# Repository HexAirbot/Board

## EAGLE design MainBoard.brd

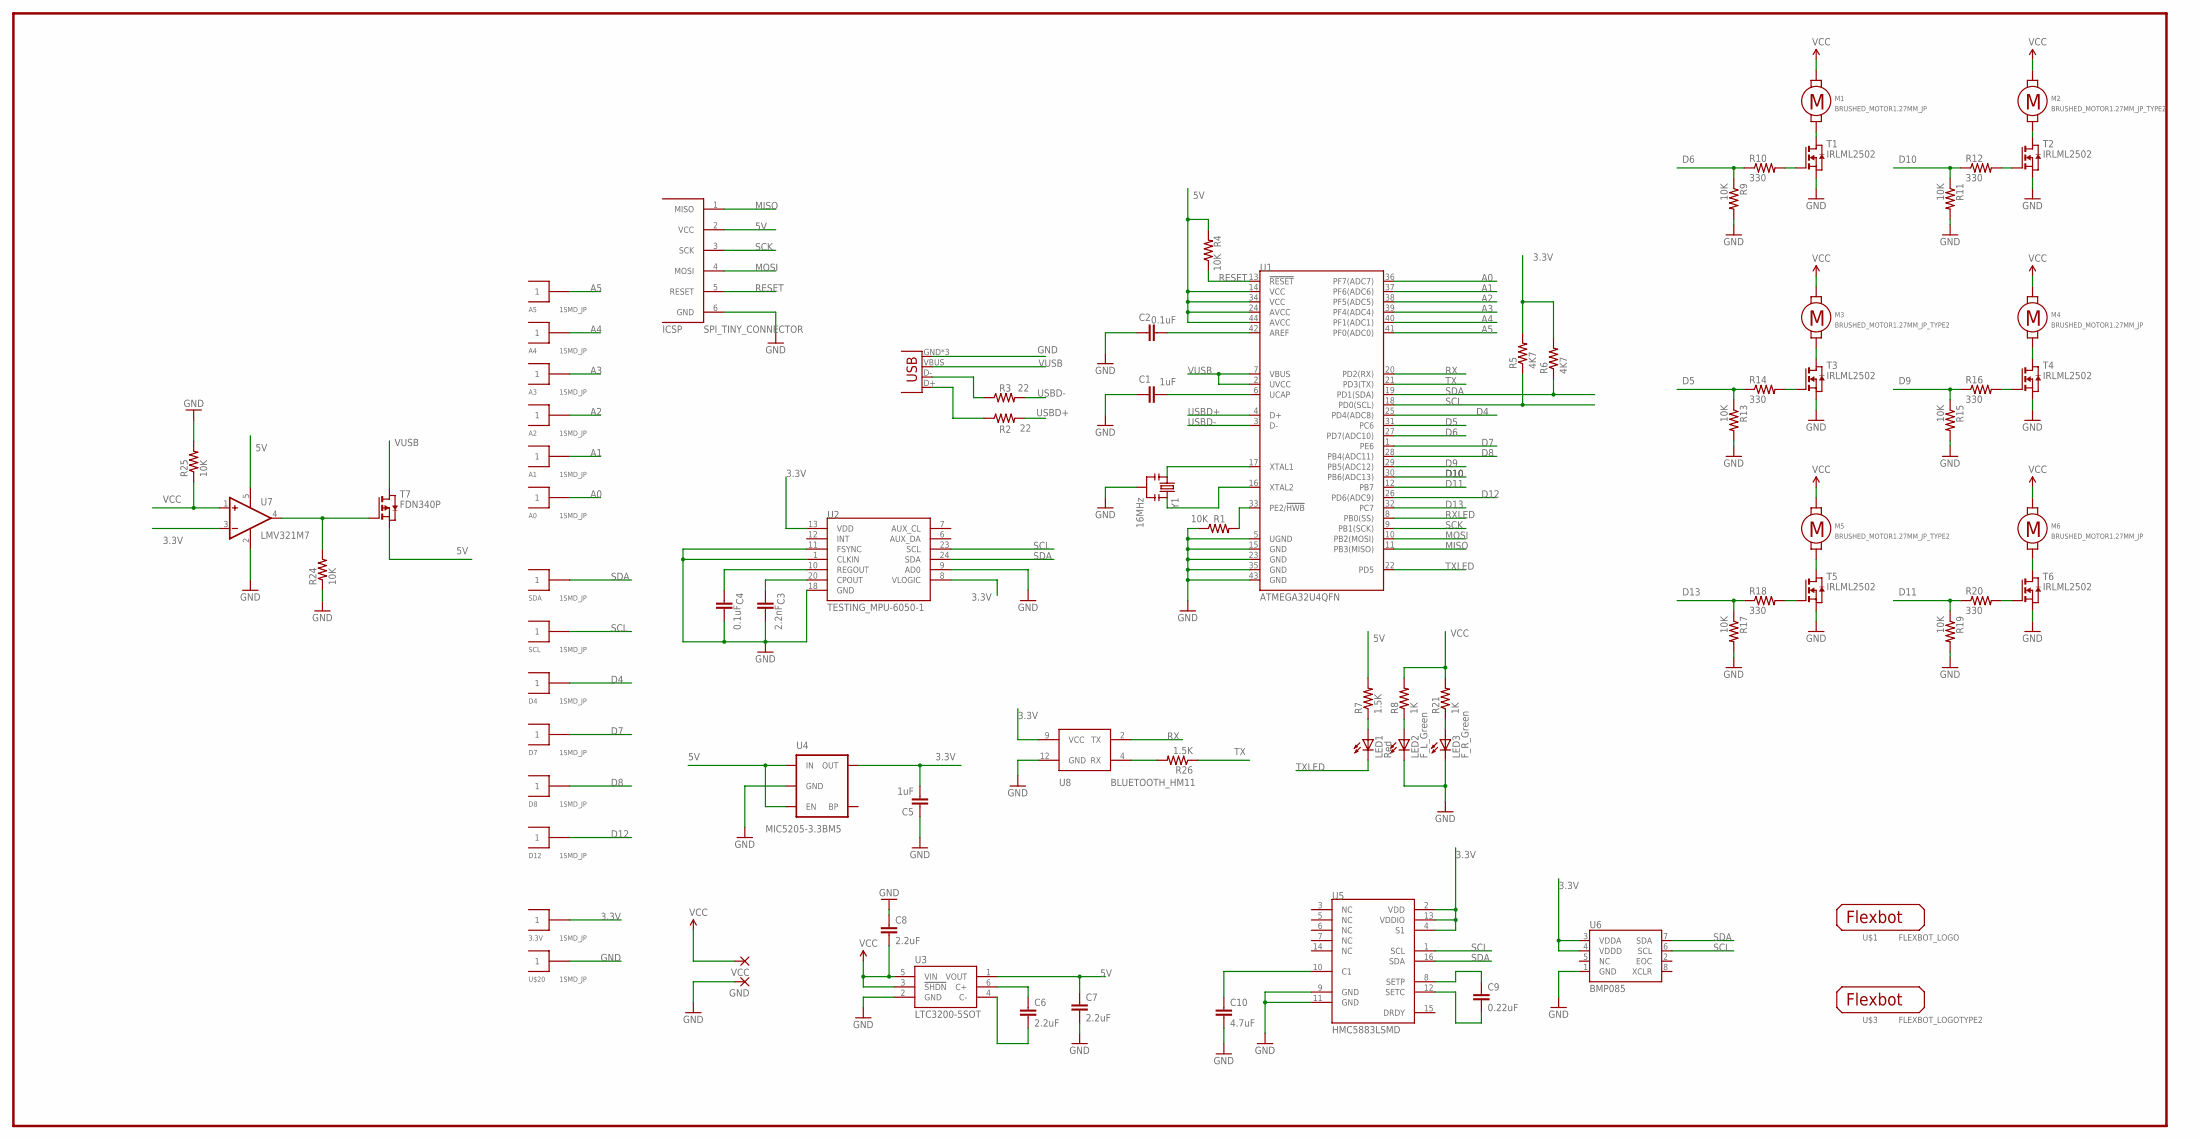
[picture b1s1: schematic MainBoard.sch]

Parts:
3.3V: 1SMD_JP; 1SMD
A0, A1, A2, A3, A4, A5: 1SMD_JP; 1SMD
C1, C5: 1uF; 0402-CAP
C2, C4: 0.1uF; 0402-CAP
C3: 2.2nF; 0402-CAP
C6, C7, C8: 2.2uF; 0603-CAP
C9: 0.22uF; 0402-CAP
C10: 4.7uF; 0603-CAP
D4, D7, D8, D12: 1SMD_JP; 1SMD
GND: 2,15/1,0
ICSP: SPI_TINY_CONNECTOR; AVR_ISP_TINY_CONNECTOR_NO_BORDER
JP1: USB-MICROB
LED1: Red; CHIPLED_0603
LED2: F_L_Green; CHIPLED_0603
LED3: F_R_Green; CHIPLED_0603
M1, M4, M6: BRUSHED_MOTOR1.27MM_JP; BRUSHED_MOTOR_1.27MM_JP
M2, M3, M5: BRUSHED_MOTOR1.27MM_JP_TYPE2; BRUSHED_MOTOR_1.27MM_JP_TYPE2
R1, R4, R9, R11, R13, R15, R17, R19, R24, R25: 10K; 0402-RES
R2, R3: 22; 0402-RES
R5, R6: 4K7; 0402-RES
R7, R26: 1.5K; 0402-RES
R8, R21: 1K; 0402-RES
R10, R12, R14, R16, R18, R20: 330; 0402-RES
SCL: 1SMD_JP; 1SMD
SDA: 1SMD_JP; 1SMD
T1, T2, T3, T4, T5, T6: IRLML2502; SOT-23
T7: FDN340P; SOT23
U1: ATMEGA32U4QFN; SPARKFUN-DIGITALIC_QFN-44
U2: TESTING_MPU-6050-1; TESTING_QFN-24-4MM2
U3: LTC3200-5SOT; SOT23-6
U4: MIC5205-3.3BM5; SOT23-5
U5: HMC5883LSMD; 16LPCC
U6: BMP085
U7: LMV321M7; SC70-5L
U8: BLUETOOTH_HM11
U$1: FLEXBOT_LOGO
U$3: FLEXBOT_LOGOTYPE2; FLEXBOT_LOGO_TYPE2
U$20: 1SMD_JP; 1SMD
VCC: 2,15/1,0
Y1: 16MHz; RESONATOR-SMD

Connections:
3.3V: 3.3V.1, C5.2, R5.2, R6.2, U2.8 (VLOGIC), U2.13 (VDD), U4.5 (OUT), U5.2 (VDD), U5.4 (S1), U5.13 (VDDIO), U6.3 (VDDA), U6.4 (VDDD), U7.3 (-IN), U8.9 (VCC)
5V: C7.1, ICSP.2 (VCC), R4.2, R7.2, T7.2 (S), U1.14 (VCC), U1.24 (AVCC), U1.34 (VCC), U1.44 (AVCC), U3.1 (VOUT), U4.1 (IN), U4.3 (EN), U7.5 (V+)
A0: A0.1, U1.36 (PF7(ADC7))
A1: A1.1, U1.37 (PF6(ADC6))
A2: A2.1, U1.38 (PF5(ADC5))
A3: A3.1, U1.39 (PF4(ADC4))
A4: A4.1, U1.40 (PF1(ADC1))
A5: A5.1, U1.41 (PF0(ADC0))
D4: D4.1, U1.25 (PD4(ADC8))
D5: R13.1, R14.1, U1.31 (PC6)
D6: R9.1, R10.1, U1.27 (PD7(ADC10))
D7: D7.1, U1.1 (PE6)
D8: D8.1, U1.28 (PB4(ADC11))
D9: R15.1, R16.1, U1.29 (PB5(ADC12))
D10: R11.1, R12.1, U1.30 (PB6(ADC13))
D11: R19.1, R20.1, U1.12 (PB7)
D12: D12.1, U1.26 (PD6(ADC9))
D13: R17.1, R18.1, U1.32 (PC7)
GND: C1.1, C2.1, C3.2, C4.2, C5.1, C7.2, C8.1, C10.2, GND.1, ICSP.6 (GND), JP1.GND, JP1.MT1 (GND), JP1.MT2 (GND), LED2.C, LED3.C, R1.1, R9.2, R11.2, R13.2, R15.2, R17.2, R19.2, R24.1, R25.2, T1.2 (S), T2.2 (S), T3.2 (S), T4.2 (S), T5.2 (S), T6.2 (S), U1.5 (UGND), U1.15 (GND), U1.23 (GND), U1.35 (GND), U1.43 (GND), U2.1 (CLKIN), U2.9 (AD0), U2.11 (FSYNC), U2.18 (GND), U3.2 (GND), U4.2 (GND), U5.9 (GND), U5.11 (GND), U6.1 (GND), U7.2 (V-), U8.12 (GND), U$20.1, Y1.2
MISO: ICSP.1 (MISO), U1.11 (PB3(MISO))
MOSI: ICSP.4 (MOSI), U1.10 (PB2(MOSI))
unnamed: U1.17 (XTAL1), Y1.1
unnamed: U1.16 (XTAL2), Y1.3
unnamed: JP1.D+, R2.1
unnamed: JP1.D-, R3.1
unnamed: C1.2, U1.6 (UCAP)
unnamed: C2.2, U1.42 (AREF)
unnamed: LED2.A, R8.1
unnamed: C4.1, U2.10 (REGOUT)
unnamed: C3.1, U2.20 (CPOUT)
unnamed: LED1.A, R7.1
unnamed: R1.2, U1.33 (PE2/!HWB)
unnamed: R18.2, T5.3 (G)
unnamed: LED3.A, R21.1
unnamed: R12.2, T2.3 (G)
unnamed: R10.2, T1.3 (G)
unnamed: M1.P$1 (1), T1.1 (D)
unnamed: M2.P$1 (1), T2.1 (D)
unnamed: R14.2, T3.3 (G)
unnamed: M3.P$1 (1), T3.1 (D)
unnamed: R16.2, T4.3 (G)
unnamed: M4.P$1 (1), T4.1 (D)
unnamed: M5.P$1 (1), T5.1 (D)
unnamed: C9.1, U5.8 (SETP)
unnamed: C6.1, U3.6 (C+)
unnamed: C6.2, U3.4 (C-)
unnamed: C9.2, U5.12 (SETC)
unnamed: C10.1, U5.10 (C1)
unnamed: R20.2, T6.3 (G)
unnamed: M6.P$1 (1), T6.1 (D)
unnamed: R24.2, T7.3 (G), U7.4 (OUT)
unnamed: R26.2, U8.4 (RX)
RESET: ICSP.5 (RESET), R4.1, U1.13 (!RESET)
RX: U1.20 (PD2(RX)), U8.2 (TX)
RXLED: U1.8 (PB0(SS))
SCK: ICSP.3 (SCK), U1.9 (PB1(SCK))
SCL: R5.1, SCL.1, U1.18 (PD0(SCL)), U2.23 (SCL), U5.1 (SCL), U6.6 (SCL)
SDA: R6.1, SDA.1, U1.19 (PD1(SDA)), U2.24 (SDA), U5.16 (SDA), U6.7 (SDA)
TX: R26.1, U1.21 (PD3(TX))
TXLED: LED1.C, U1.22 (PD5)
USBD+: R2.2, U1.4 (D+)
USBD-: R3.2, U1.3 (D-)
VCC: C8.2, M1.P$2 (2), M2.P$2 (2), M3.P$2 (2), M4.P$2 (2), M5.P$2 (2), M6.P$2 (2), R8.2, R21.2, R25.1, U3.3 (!SHDN), U3.5 (VIN), U7.1 (+IN), VCC.1
VUSB: JP1.VBUS, T7.1 (D), U1.2 (UVCC), U1.7 (VBUS)

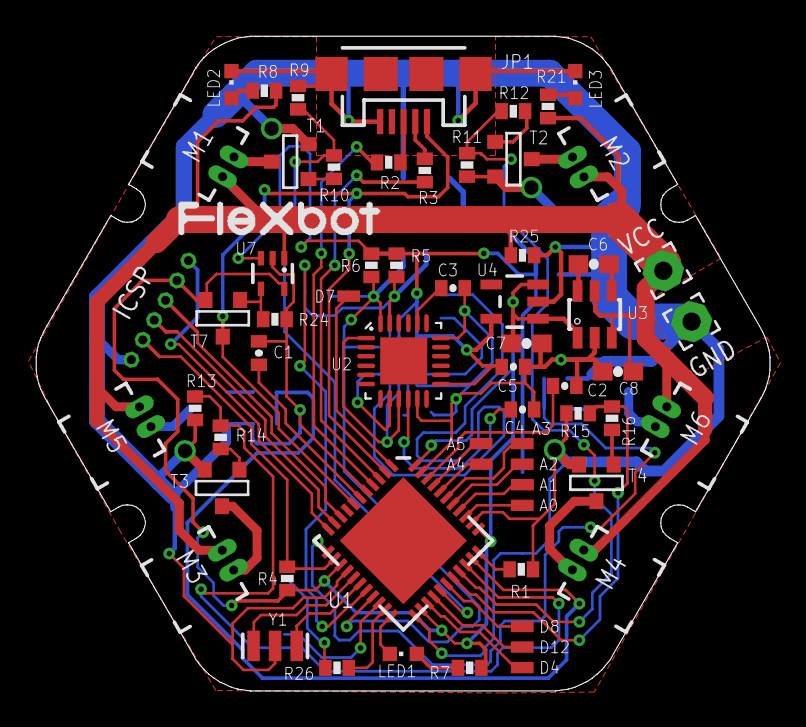
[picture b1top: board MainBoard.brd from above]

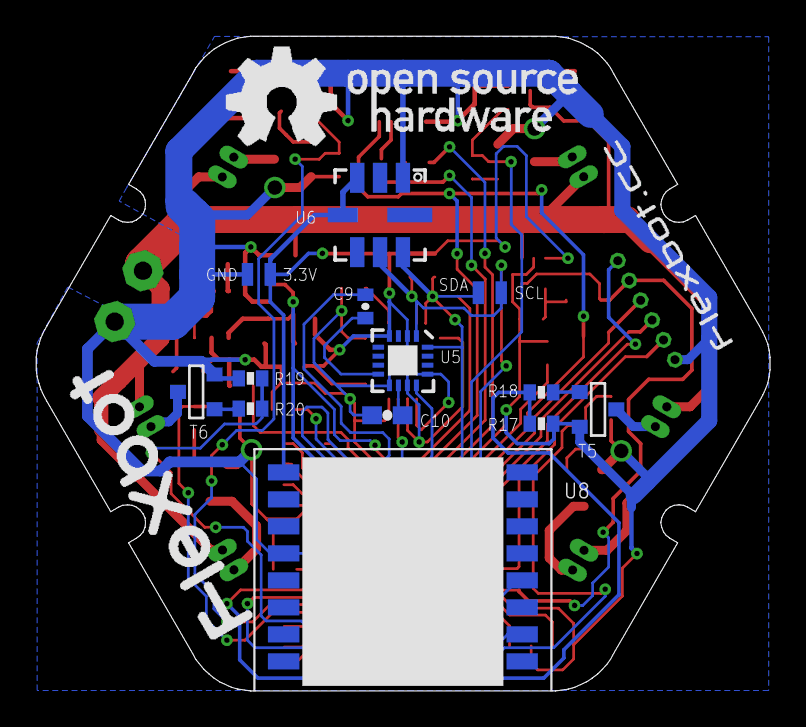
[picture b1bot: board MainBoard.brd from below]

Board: 2 copper layers, 40.8 x 36.4 mm, 79 parts (16 on the bottom side), 63 nets.

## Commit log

2013-12-26 "board design file"
2014-01-20 added license
2014-01-20 added schematic file

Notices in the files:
parts and their libraries:
SparkFun-DigitalIC: Licensing: CC v3.0 Share-Alike You are welcome to use this library for commercial purposes.
